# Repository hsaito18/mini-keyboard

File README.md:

# mini-keyboard
Building a 4x4 macro keyboard using left-over Cherry MX Red key switches and left-over keycaps. Will use AT90USB1286 microcontroller, since the typical ATMega microcontroller is unavailable.

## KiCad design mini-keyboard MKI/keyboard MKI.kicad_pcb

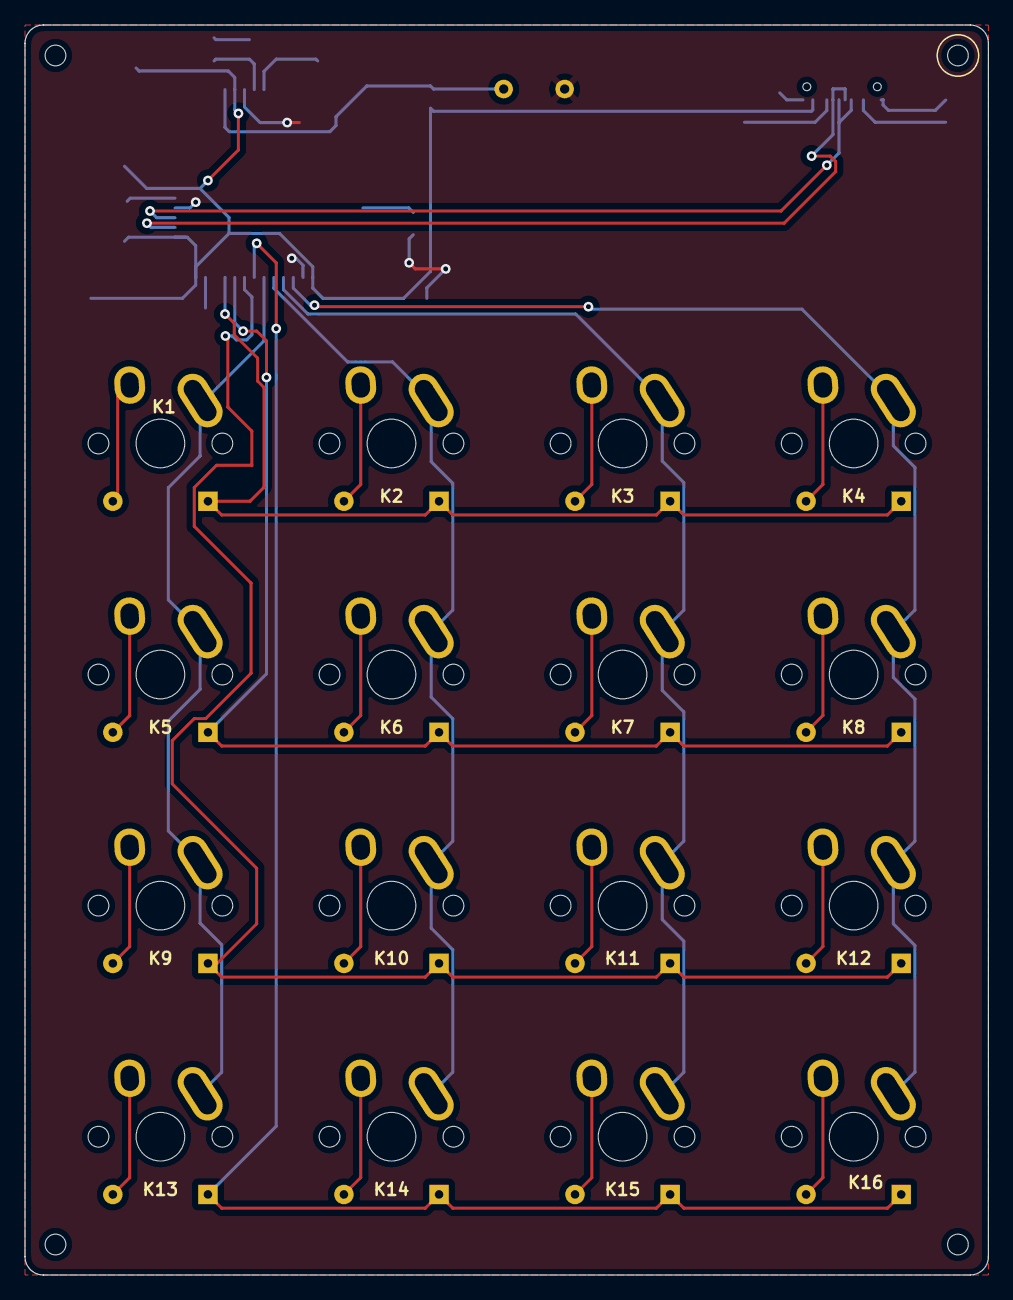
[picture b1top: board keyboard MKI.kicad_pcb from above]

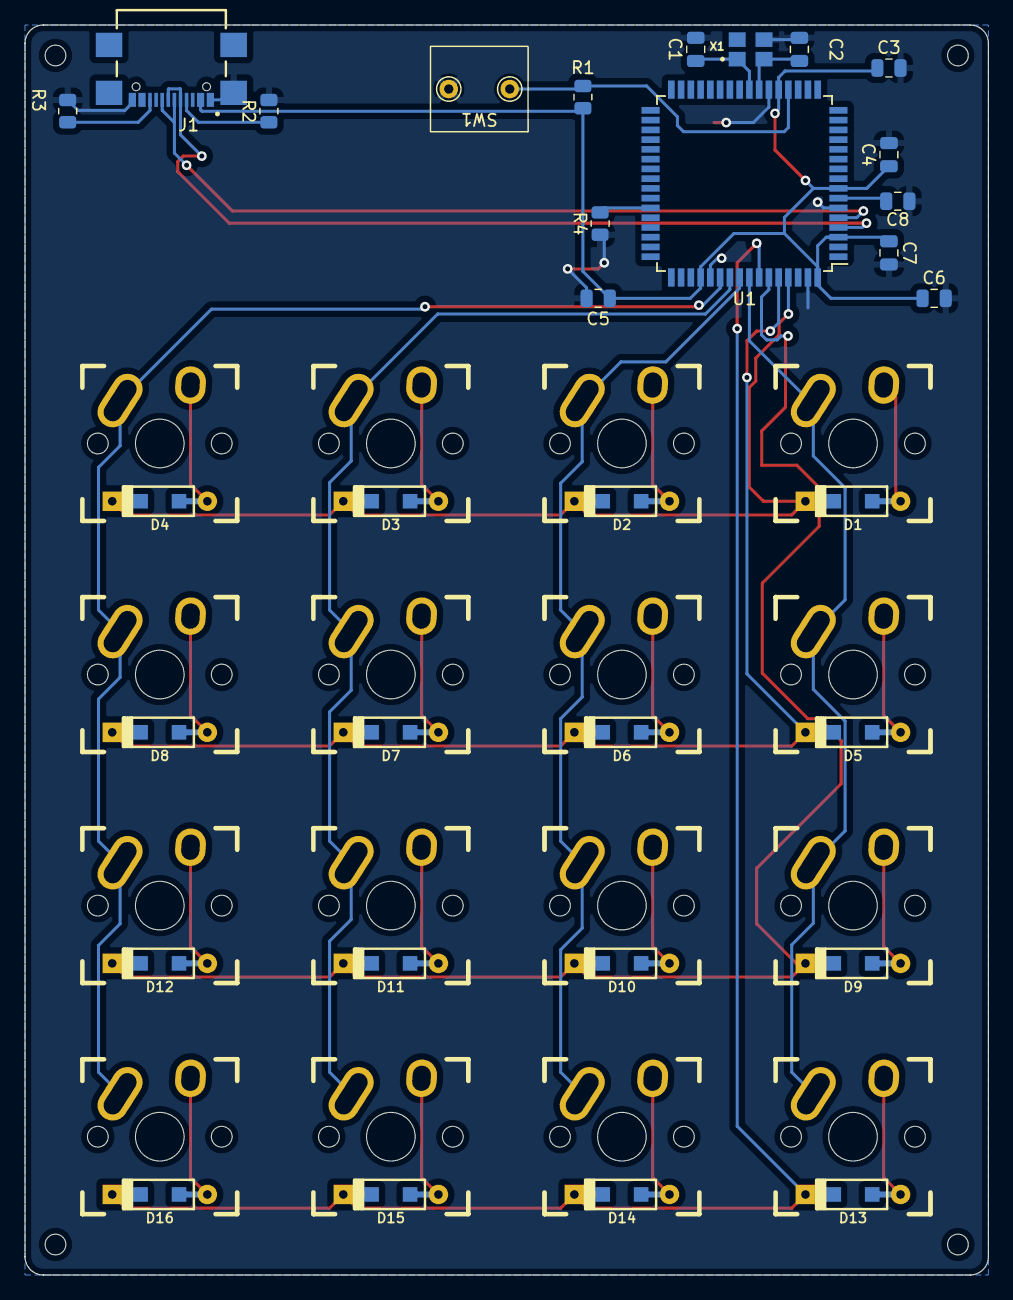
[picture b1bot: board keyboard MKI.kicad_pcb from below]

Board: 2 copper layers, 79.0 x 102.5 mm, 48 parts (48 on the bottom side), 35 nets.

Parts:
C1, C2: 22p; C_0805_2012Metric
C3, C4, C5, C6: 0.1u; C_0805_2012Metric
C7: 4.7u; C_0805_2012Metric
C8: 1u; C_0805_2012Metric
D1, D2, D3, D4, D5, D6, D7, D8, D9, D10, D11, D12, D13, D14, D15, D16: D; D_SOD123_axial
J1: USB_C_Receptacle_USB2.0; GCT_USB4110-GF-A_REVB
K1, K2, K3, K4, K5, K6, K7, K8, K9, K10, K11, K12, K13, K14, K15, K16: KEYSW; Mx_Alps_100
R1, R4: 10k; R_0805_2012Metric
R2, R3: 5.1k; R_0805_2012Metric
SW1: SW_PUSH; b3f-6000
U1: AT90USB1286-AU; TQFP-64_14x14mm_P0.8mm
X1: XTAL_GND; XTAL_403C35E26M00000

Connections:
GND: C1.2, C2.2, C3.2, C4.2, C5.2, C6.2, C7.2, C8.1, J1.A1/B12, J1.B1/A12, J1.S1 (SHIELD), R2.2, R3.2, R4.1, SW1.1, U1.6 (UGND), U1.22 (GND), U1.53 (GND), U1.63 (GND), X1.3
unnamed: C1.1, U1.24 (XTAL1), X1.1
unnamed: C2.1, U1.23 (XTAL2), X1.2
unnamed: C8.2, U1.7 (UCAP)
unnamed: D1.2 (A), K1.2
unnamed: D2.2 (A), K2.2
unnamed: D3.2 (A), K3.2
unnamed: D4.2 (A), K4.2
unnamed: D5.2 (A), K5.2
unnamed: D6.2 (A), K6.2
unnamed: D7.2 (A), K7.2
unnamed: D8.2 (A), K8.2
unnamed: D9.2 (A), K9.2
unnamed: D10.2 (A), K10.2
unnamed: D11.2 (A), K11.2
unnamed: D12.2 (A), K12.2
unnamed: D13.2 (A), K13.2
unnamed: D14.2 (A), K14.2
unnamed: D15.2 (A), K15.2
unnamed: D16.2 (A), K16.2
unnamed: J1.A5 (CC1), R2.1
unnamed: J1.A6 (D+), J1.B6 (D+), U1.5 (D+)
unnamed: J1.A7 (D-), J1.B7 (D-), U1.4 (D-)
unnamed: J1.B5 (CC2), R3.1
unnamed: R1.2, SW1.2, U1.20 (~RESET)
unnamed: R4.2, U1.43 (PE2/~HWB)
VCC: C3.1, C4.1, C5.1, C6.1, C7.1, J1.A4/B9, R1.1, U1.3 (UVCC), U1.8 (VBUS), U1.21 (VCC), U1.52 (VCC), U1.64 (AVCC)
col0: K1.1, K5.1, K9.1, K13.1, U1.57 (PF4)
col1: K2.1, K6.1, K10.1, K14.1, U1.56 (PF5)
col2: K3.1, K7.1, K11.1, K15.1, U1.55 (PF6)
col3: K4.1, K8.1, K12.1, K16.1, U1.54 (PF7)
row0: D1.1 (K), D2.1 (K), D3.1 (K), D4.1 (K), U1.61 (PF0)
row1: D5.1 (K), D6.1 (K), D7.1 (K), D8.1 (K), U1.60 (PF1)
row2: D9.1 (K), D10.1 (K), D11.1 (K), D12.1 (K), U1.59 (PF2)
row3: D13.1 (K), D14.1 (K), D15.1 (K), D16.1 (K), U1.58 (PF3)

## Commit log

2021-08-16 init
2021-08-16 removed recursive repository
2021-08-16 added pdf
2021-08-16 renamed pdf
2021-09-01 added v1 kb firmware
2021-09-01 added BM and plate drawing
2021-09-01 updated readmes and notes.
2021-09-02 added keyboard MKII
2021-09-02 added case stl file
2021-09-02 added through holes to case
2021-09-03 idk wtf these files are but whatever
2021-09-03 added midi keymap take 1
2022-05-11 idk lol
2022-05-11 pdfs
2022-05-11 added initial Altium version of MKII
2022-05-11 more progress on altium
2022-05-12 added crystal to altium schematic
2022-05-16 started PCB layout in Altium version
2022-05-19 some changes idk
2022-06-02 did most of the PCB overlay, still need to do VCC and GND connections.
2022-06-02 added scratch notes
2022-06-02 added VCC and GND connections, still have to fix design rule violations.
2022-06-09 down to 11 rule violations.
2022-06-09 fixed all rule violations, should be ready?
2022-06-10 exported and ordered
2022-06-11 added list of leftover components
2022-07-21 STEP file output plus other stuff idk
